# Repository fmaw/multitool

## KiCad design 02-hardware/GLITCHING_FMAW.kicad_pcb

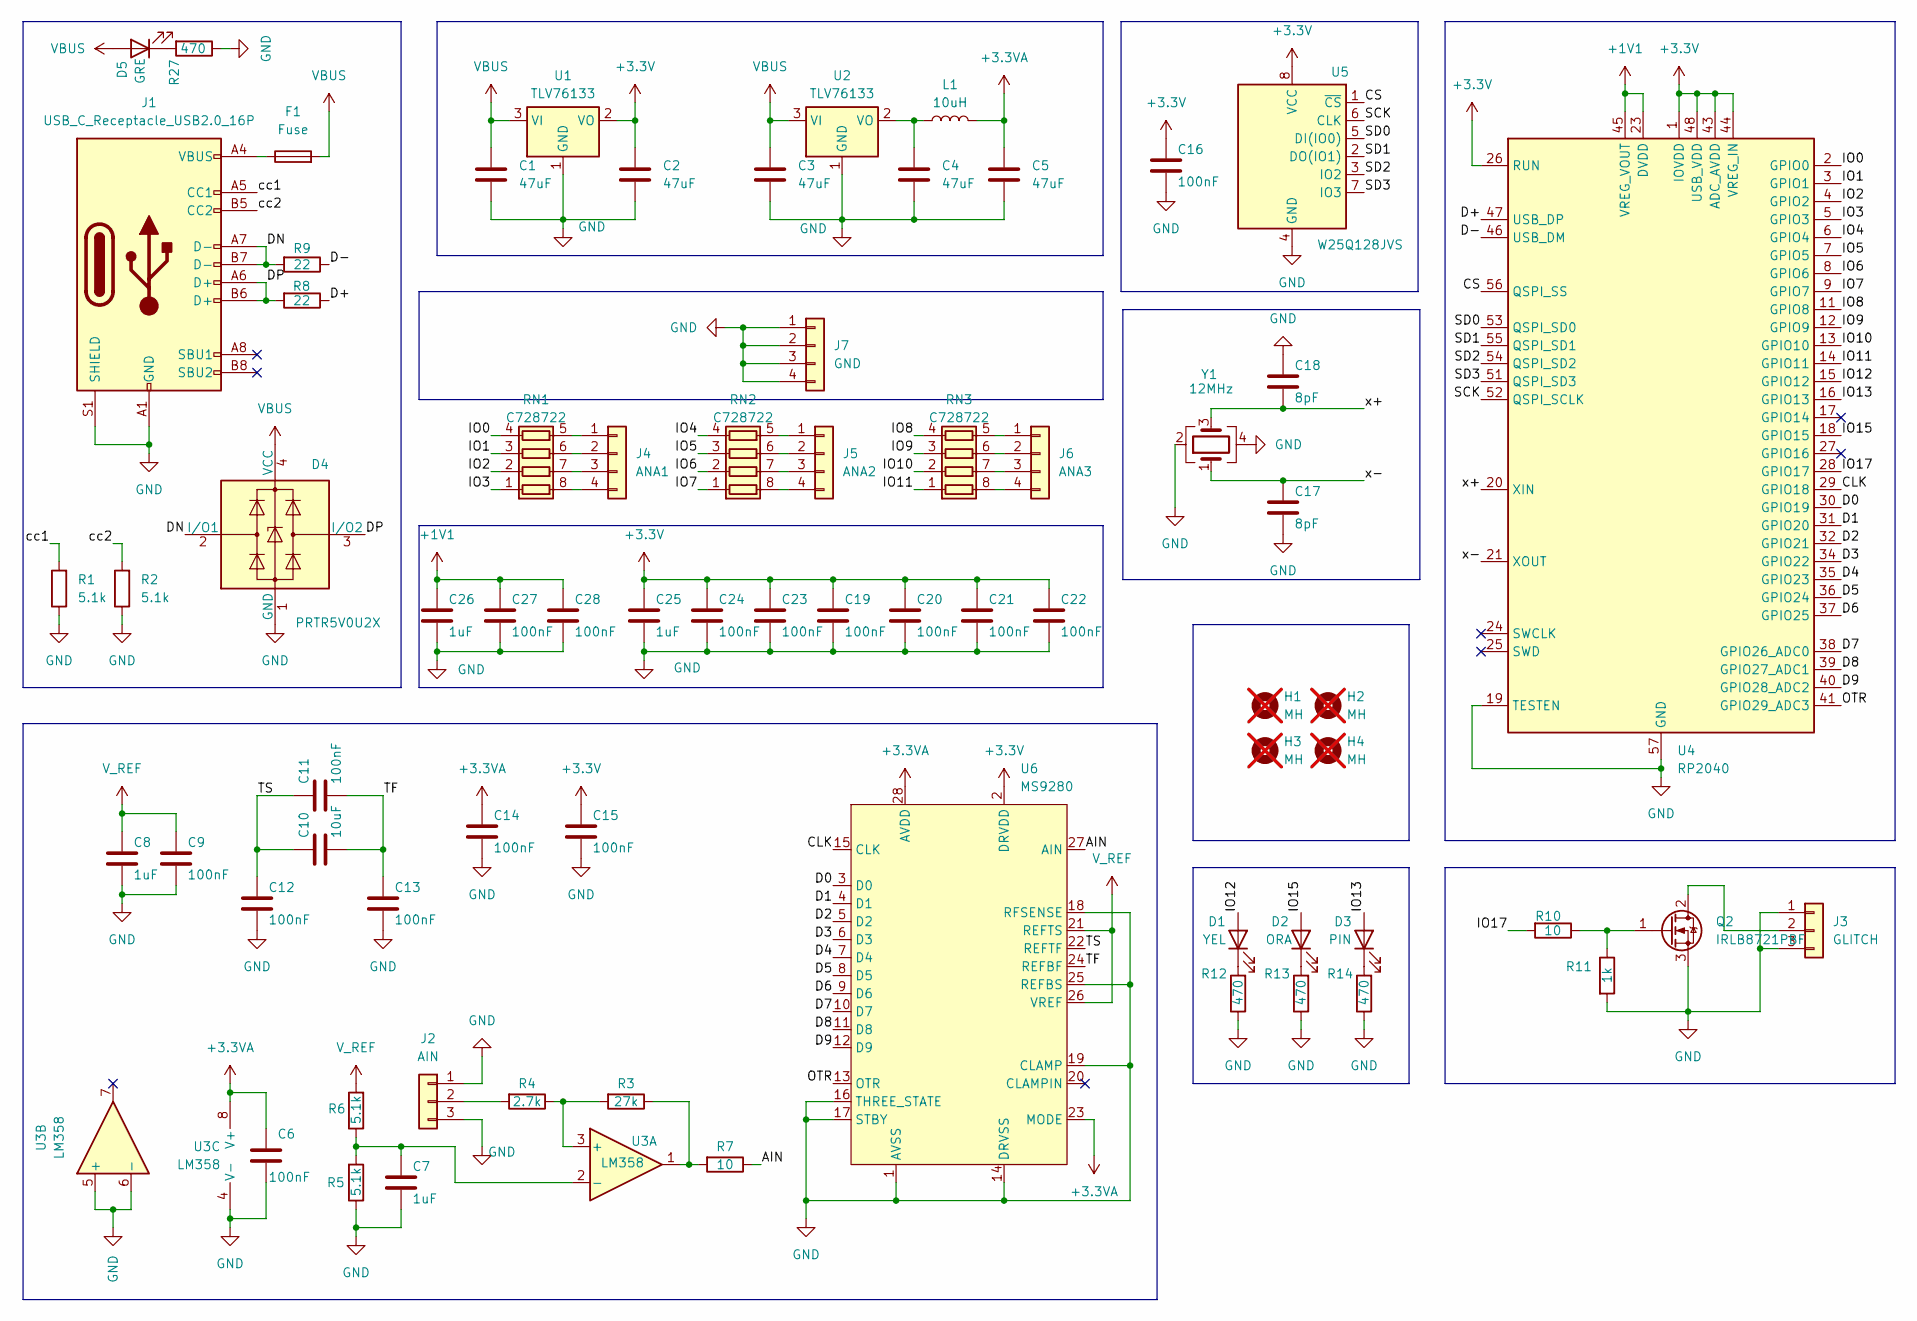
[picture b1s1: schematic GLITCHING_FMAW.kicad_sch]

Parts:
C1, C2, C3, C4, C5: 47uF; C_1206_3216Metric
C6, C9, C11, C12, C13, C14, C15, C16, C19, C20, C21, C22, C23, C24, C27, C28: 100nF; C_0603_1608Metric
C7, C8, C25, C26: 1uF; C_0603_1608Metric
C10: 10uF; C_0603_1608Metric
C17, C18: 8pF; C_0603_1608Metric
D1: YEL; LED_0603_1608Metric
D2: ORA; LED_0603_1608Metric
D3: PIN; LED_0603_1608Metric
D4: PRTR5V0U2X; SOT-143; LCSC C5180302
D5: GRE; LED_0603_1608Metric
F1: Fuse; Fuse_1812_4532Metric; LCSC C142689
H1, H2, H3, H4: MH; MountingHole_2.2mm_M2_DIN965_Pad; not fitted
J1: USB_C_Receptacle_USB2.0_16P; USB_C_Receptacle_GCT_USB4105-xx-A_16P_TopMnt_Horizontal
J2: AIN; PinHeader_1x03_P2.54mm_Vertical
J3: GLITCH; PinHeader_1x03_P2.54mm_Vertical
J4: ANA1; PinHeader_1x04_P2.54mm_Vertical
J5: ANA2; PinHeader_1x04_P2.54mm_Vertical
J6: ANA3; PinHeader_1x04_P2.54mm_Vertical
J7: GND; PinHeader_1x04_P2.54mm_Vertical
L1: 10uH; L_Bourns_SRP7028A_7.3x6.6mm; LCSC C22463829
Q2: IRLB8721PBF; SOT-223-3_TabPin2; LCSC C73298
R1, R2, R5, R6: 5.1k; R_0603_1608Metric
R3: 27k; R_0603_1608Metric
R4: 2.7k; R_0603_1608Metric
R7, R10: 10; R_0603_1608Metric
R8, R9: 22; R_0603_1608Metric
R11: 1k; R_0603_1608Metric
R12, R13, R14, R27: 470; R_0603_1608Metric
RN1, RN2, RN3: C728722; R_Array_Concave_4x0402; LCSC C728722
U1, U2: TLV76133; SOT-223-3_TabPin2; LCSC C7527500
U3: LM358; SO-8_3.9x4.9mm_P1.27mm; LCSC C693063
U4: RP2040; QFN-56-1EP_7x7mm_P0.4mm_EP3.2x3.2mm
U5: W25Q128JVS; SOIC-8_5.23x5.23mm_P1.27mm; LCSC C97521
U6: MS9280; SSOP-28_5.3x10.2mm_P0.65mm; LCSC C1509021
Y1: 12MHz; Crystal_SMD_Abracon_ABM10-4Pin_2.5x2.0mm; LCSC C1985454

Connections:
+1V1: C26.1, C27.1, C28.1, U4.23 (DVDD), U4.45 (VREG_VOUT), U4.50 (DVDD)
+3.3V: C2.1, C15.1, C16.1, C19.1, C20.1, C21.1, C22.1, C23.1, C24.1, C25.1, U1.2 (VO), U4.1 (IOVDD), U4.10 (IOVDD), U4.22 (IOVDD), U4.26 (RUN), U4.33 (IOVDD), U4.42 (IOVDD), U4.43 (ADC_AVDD), U4.44 (VREG_IN), U4.48 (USB_VDD), U4.49 (IOVDD), U5.8 (VCC), U6.2 (DRVDD)
+3.3VA: C5.1, C6.1, C14.1, L1.2, U3.8 (V+), U6.23 (MODE), U6.28 (AVDD)
/AIN: R7.1, U6.27 (AIN)
/CLK: U4.29 (GPIO18), U6.15 (CLK)
/CS: U4.56 (QSPI_SS), U5.1 (~CS)
/D0: U4.30 (GPIO19), U6.3 (D0)
/D1: U4.31 (GPIO20), U6.4 (D1)
/D2: U4.32 (GPIO21), U6.5 (D2)
/D3: U4.34 (GPIO22), U6.6 (D3)
/D4: U4.35 (GPIO23), U6.7 (D4)
/D5: U4.36 (GPIO24), U6.8 (D5)
/D6: U4.37 (GPIO25), U6.9 (D6)
/D7: U4.38 (GPIO26_ADC0), U6.10 (D7)
/D8: U4.39 (GPIO27_ADC1), U6.11 (D8)
/D9: U4.40 (GPIO28_ADC2), U6.12 (D9)
/D+: R8.1, U4.47 (USB_DP)
/D-: R9.1, U4.46 (USB_DM)
/DN: D4.2 (I/O1), J1.A7 (D-), J1.B7 (D-), R9.2
/DP: D4.3 (I/O2), J1.A6 (D+), J1.B6 (D+), R8.2
/IO0: RN1.4 (R4.1), U4.2 (GPIO0)
/IO1: RN1.3 (R3.1), U4.3 (GPIO1)
/IO2: RN1.2 (R2.1), U4.4 (GPIO2)
/IO3: RN1.1 (R1.1), U4.5 (GPIO3)
/IO4: RN2.4 (R4.1), U4.6 (GPIO4)
/IO5: RN2.3 (R3.1), U4.7 (GPIO5)
/IO6: RN2.2 (R2.1), U4.8 (GPIO6)
/IO7: RN2.1 (R1.1), U4.9 (GPIO7)
/IO8: RN3.4 (R4.1), U4.11 (GPIO8)
/IO9: RN3.3 (R3.1), U4.12 (GPIO9)
/IO10: RN3.2 (R2.1), U4.13 (GPIO10)
/IO11: RN3.1 (R1.1), U4.14 (GPIO11)
/IO12: D1.2 (A), U4.15 (GPIO12)
/IO13: D3.2 (A), U4.16 (GPIO13)
/IO15: D2.2 (A), U4.18 (GPIO15)
/IO17: R10.2, U4.28 (GPIO17)
/OTR: U4.41 (GPIO29_ADC3), U6.13 (OTR)
/SCK: U4.52 (QSPI_SCLK), U5.6 (CLK)
/SD0: U4.53 (QSPI_SD0), U5.5 (DI(IO0))
/SD1: U4.55 (QSPI_SD1), U5.2 (DO(IO1))
/SD2: U4.54 (QSPI_SD2), U5.3 (IO2)
/SD3: U4.51 (QSPI_SD3), U5.7 (IO3)
/TF: C10.2, C11.2, C13.1, U6.24 (REFBF)
/TS: C10.1, C11.1, C12.1, U6.22 (REFTF)
/cc1: J1.A5 (CC1), R1.2
/cc2: J1.B5 (CC2), R2.2
/x+: C18.2, U4.20 (XIN), Y1.3
/x-: C17.1, U4.21 (XOUT), Y1.1
GND: C1.2, C2.2, C3.2, C4.2, C5.2, C6.2, C7.2, C8.2, C9.2, C12.2, C13.2, C14.2, C15.2, C16.2, C17.2, C18.1, C19.2, C20.2, C21.2, C22.2, C23.2, C24.2, C25.2, C26.2, C27.2, C28.2, D4.1 (GND), J1.A1 (GND), J1.A12 (GND), J1.B1 (GND), J1.B12 (GND), J1.S1 (SHIELD), J2.1, J2.3, J3.1, J3.3, J7.1, J7.2, J7.3, J7.4, Q2.3 (S), R1.1, R2.1, R5.1, R11.2, R12.1, R13.1, R14.1, R27.1, U1.1 (GND), U2.1 (GND), U3.4 (V-), U3.5 (+), U3.6 (-), U4.19 (TESTEN), U4.57 (GND), U5.4 (GND), U6.1 (AVSS), U6.14 (DRVSS), U6.16 (THREE_STATE), U6.17 (STBY), U6.18 (RFSENSE), U6.19 (CLAMP), U6.25 (REFBS), Y1.2, Y1.4
unnamed: D1.1 (K), R12.2
unnamed: D2.1 (K), R13.2
unnamed: D3.1 (K), R14.2
unnamed: D5.1 (K), R27.2
unnamed: F1.1, J1.A4 (VBUS), J1.A9 (VBUS), J1.B4 (VBUS), J1.B9 (VBUS)
unnamed: J2.2, R4.2
unnamed: J3.2, Q2.2 (D)
unnamed: J4.1, RN1.5 (R4.2)
unnamed: J4.2, RN1.6 (R3.2)
unnamed: J4.3, RN1.7 (R2.2)
unnamed: J4.4, RN1.8 (R1.2)
unnamed: J5.1, RN2.5 (R4.2)
unnamed: J5.2, RN2.6 (R3.2)
unnamed: J5.3, RN2.7 (R2.2)
unnamed: J5.4, RN2.8 (R1.2)
unnamed: J6.1, RN3.5 (R4.2)
unnamed: J6.2, RN3.6 (R3.2)
unnamed: J6.3, RN3.7 (R2.2)
unnamed: J6.4, RN3.8 (R1.2)
unnamed: Q2.1 (G), R10.1, R11.1
unnamed: R3.1, R7.2, U3.1
unnamed: C4.1, L1.1, U2.2 (VO)
unnamed: R3.2, R4.1, U3.3 (+)
unnamed: C7.1, R5.2, R6.1, U3.2 (-)
VBUS: C1.1, C3.1, D4.4 (VCC), D5.2 (A), F1.2, U1.3 (VI), U2.3 (VI)
V_REF: C8.1, C9.1, R6.2, U6.21 (REFTS), U6.26 (VREF)

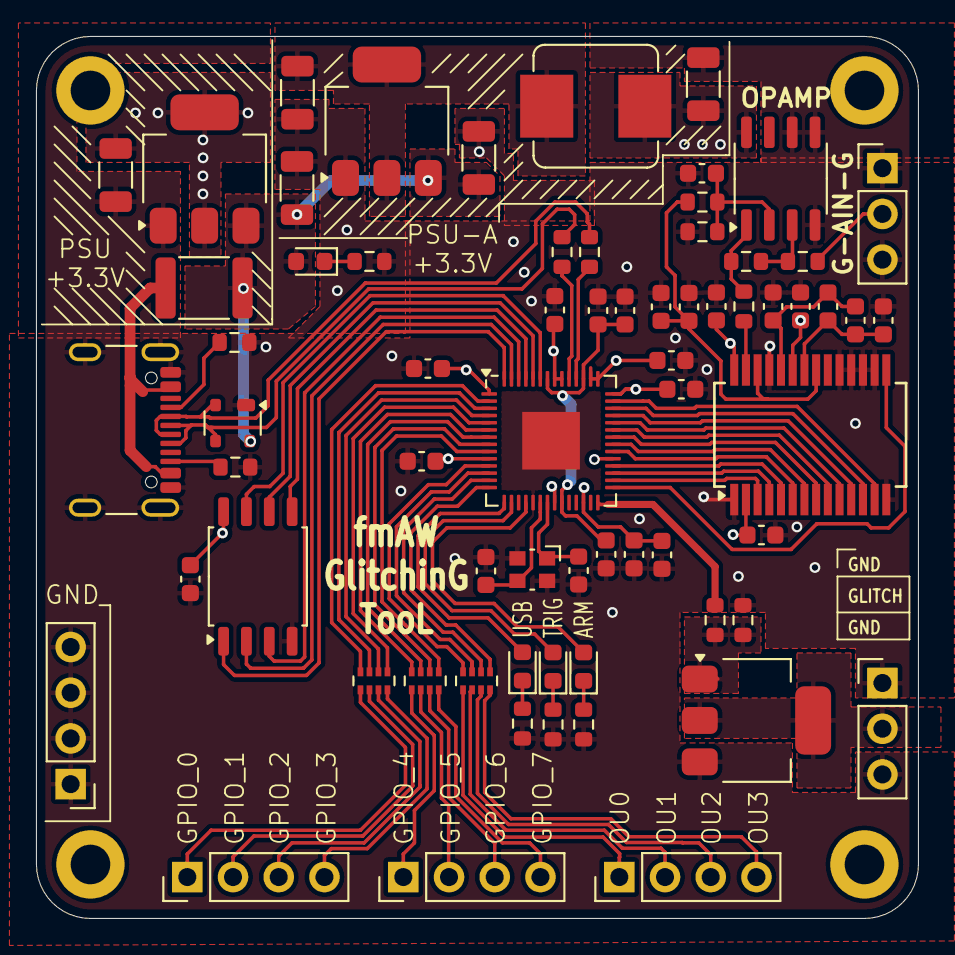
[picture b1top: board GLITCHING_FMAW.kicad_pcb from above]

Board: 4 copper layers, 49.0 x 49.0 mm, 72 parts (0 on the bottom side), 75 nets.

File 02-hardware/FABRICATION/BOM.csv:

Reference,Value,Footprint,Qty,DNP,LCSC
C1,47uF,Capacitor_SMD:C_1206_3216Metric,1,,
C2,47uF,Capacitor_SMD:C_1206_3216Metric,1,,
C3,47uF,Capacitor_SMD:C_1206_3216Metric,1,,
C4,47uF,Capacitor_SMD:C_1206_3216Metric,1,,
C5,47uF,Capacitor_SMD:C_1206_3216Metric,1,,
C6,100nF,Capacitor_SMD:C_0603_1608Metric,1,,
C7,1uF,Capacitor_SMD:C_0603_1608Metric,1,,
C8,1uF,Capacitor_SMD:C_0603_1608Metric,1,,
C9,100nF,Capacitor_SMD:C_0603_1608Metric,1,,
C10,10uF,Capacitor_SMD:C_0603_1608Metric,1,,
C11,100nF,Capacitor_SMD:C_0603_1608Metric,1,,
C12,100nF,Capacitor_SMD:C_0603_1608Metric,1,,
C13,100nF,Capacitor_SMD:C_0603_1608Metric,1,,
C14,100nF,Capacitor_SMD:C_0603_1608Metric,1,,
C15,100nF,Capacitor_SMD:C_0603_1608Metric,1,,
C16,100nF,Capacitor_SMD:C_0603_1608Metric,1,,
C17,8pF,Capacitor_SMD:C_0603_1608Metric,1,,
C18,8pF,Capacitor_SMD:C_0603_1608Metric,1,,
C19,100nF,Capacitor_SMD:C_0603_1608Metric,1,,
C20,100nF,Capacitor_SMD:C_0603_1608Metric,1,,
C21,100nF,Capacitor_SMD:C_0603_1608Metric,1,,
C22,100nF,Capacitor_SMD:C_0603_1608Metric,1,,
C23,100nF,Capacitor_SMD:C_0603_1608Metric,1,,
C24,100nF,Capacitor_SMD:C_0603_1608Metric,1,,
C25,1uF,Capacitor_SMD:C_0603_1608Metric,1,,
C26,1uF,Capacitor_SMD:C_0603_1608Metric,1,,
C27,100nF,Capacitor_SMD:C_0603_1608Metric,1,,
C28,100nF,Capacitor_SMD:C_0603_1608Metric,1,,
D1,YEL,LED_SMD:LED_0603_1608Metric,1,,
D2,ORA,LED_SMD:LED_0603_1608Metric,1,,
D3,PIN,LED_SMD:LED_0603_1608Metric,1,,
D4,PRTR5V0U2X,Package_TO_SOT_SMD:SOT-143,1,,C5180302
D5,GRE,LED_SMD:LED_0603_1608Metric,1,,
F1,Fuse,Fuse:Fuse_1812_4532Metric,1,,C142689 
J1,USB_C_Receptacle_USB2.0_16P,Connector_USB:USB_C_Receptacle_GCT_USB4105-xx-A_16P_TopMnt_Horizontal,1,,
J2,AIN,Connector_PinHeader_2.54mm:PinHeader_1x03_P2.54mm_Vertical,1,,
J3,GLITCH,Connector_PinHeader_2.54mm:PinHeader_1x03_P2.54mm_Vertical,1,,
J4,ANA1,Connector_PinHeader_2.54mm:PinHeader_1x04_P2.54mm_Vertical,1,,
J5,ANA2,Connector_PinHeader_2.54mm:PinHeader_1x04_P2.54mm_Vertical,1,,
J6,ANA3,Connector_PinHeader_2.54mm:PinHeader_1x04_P2.54mm_Vertical,1,,
J7,GND,Connector_PinHeader_2.54mm:PinHeader_1x04_P2.54mm_Vertical,1,,
L1,10uH,Inductor_SMD:L_Bourns_SRP7028A_7.3x6.6mm,1,,C22463829
Q2,IRLB8721PBF,Package_TO_SOT_SMD:SOT-223-3_TabPin2,1,,C73298
R1,5.1k,Resistor_SMD:R_0603_1608Metric,1,,
R2,5.1k,Resistor_SMD:R_0603_1608Metric,1,,
R3,27k,Resistor_SMD:R_0603_1608Metric,1,,
R4,2.7k,Resistor_SMD:R_0603_1608Metric,1,,
R5,5.1k,Resistor_SMD:R_0603_1608Metric,1,,
R6,5.1k,Resistor_SMD:R_0603_1608Metric,1,,
R7,10,Resistor_SMD:R_0603_1608Metric,1,,
R8,22,Resistor_SMD:R_0603_1608Metric,1,,
R9,22,Resistor_SMD:R_0603_1608Metric,1,,
R10,10,Resistor_SMD:R_0603_1608Metric,1,,
R11,1k,Resistor_SMD:R_0603_1608Metric,1,,
R12,470,Resistor_SMD:R_0603_1608Metric,1,,
R13,470,Resistor_SMD:R_0603_1608Metric,1,,
R14,470,Resistor_SMD:R_0603_1608Metric,1,,
R27,470,Resistor_SMD:R_0603_1608Metric,1,,
RN1,C728722,Resistor_SMD:R_Array_Concave_4x0402,1,,C728722
RN2,C728722,Resistor_SMD:R_Array_Concave_4x0402,1,,C728722
RN3,C728722,Resistor_SMD:R_Array_Concave_4x0402,1,,C728722
U1,TLV76133,Package_TO_SOT_SMD:SOT-223-3_TabPin2,1,,C7527500
U2,TLV76133,Package_TO_SOT_SMD:SOT-223-3_TabPin2,1,,C7527500
U3,LM358,Package_SO:SO-8_3.9x4.9mm_P1.27mm,1,,C693063
U4,RP2040,Package_DFN_QFN:QFN-56-1EP_7x7mm_P0.4mm_EP3.2x3.2mm,1,,
U5,W25Q128JVS,Package_SO:SOIC-8_5.23x5.23mm_P1.27mm,1,,C97521
U6,MS9280,Package_SO:SSOP-28_5.3x10.2mm_P0.65mm,1,,C1509021
Y1,12MHz,Crystal:Crystal_SMD_Abracon_ABM10-4Pin_2.5x2.0mm,1,,C1985454

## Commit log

2024-10-13 minor changes to convert into 2 layers board
2024-10-13 review fabrication files
2025-03-05 v1-2layer
2025-03-05 v1-layer
2025-04-03 updated gerber fabrication
2025-04-03 organization project's files
2025-04-03 add source code + builded firmware
